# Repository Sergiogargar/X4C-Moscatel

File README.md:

# X4C-Moscatel — Firmware ESP32

Nodo IoT de borde para monitorización de infraestructura ferroviaria.  
Captura la firma vibratoria del tren mediante el IMU ICM-20948, la geolocaliza
con el GPS NEO-6M y publica los datos en tiempo real vía MQTT para alimentar
el dashboard de visualización.

---

## Puesta en marcha

### Requisitos previos

- [ESP-IDF](https://docs.espressif.com/projects/esp-idf/en/latest/esp32s3/get-started/) v5.x instalado y configurado
- Docker + Docker Compose (para el backend)
- El ESP32-S3 conectado por USB

---

### Paso 1 — Obtener la IP del host

El ESP32 publica los datos MQTT al host donde corre Docker.
Antes de compilar, averigua su IP (deben estar en la misma red WiFi):

```bash
# Windows
ipconfig

# Mac / Linux
ifconfig   # o: ip route get 1 | awk '{print $7}'
```

---

### Paso 2 — Configurar el firmware

Abre **`codeina/train_digital_twin/main/network_task.cpp`** y rellena las
macros al inicio del archivo:

```c
// ─── CONFIGURAR ANTES DE FLASHEAR ────────────────────────────────
#define WIFI_SSID       "NOMBRE_DE_TU_RED"        // ← SSID de tu red WiFi
#define WIFI_PASS       "CONTRASEÑA_DE_TU_RED"    // ← Contraseña WiFi
#define MQTT_BROKER_URI "mqtt://192.168.X.X:1883" // ← IP del host del paso 1
#define TRAIN_ID        "T-101"  // ← ID único por unidad (T-101, T-102, ...)
```

> Si tienes varios ESP32, cada uno debe tener un `TRAIN_ID` distinto.

---

### Paso 3 — Arrancar el backend Docker

```bash
cd codeina/train_digital_twin/backend
docker-compose up -d
```

Comprueba que los cuatro contenedores están corriendo:

```bash
docker-compose ps
```

| Servicio | Puerto | Descripción |
|---|---|---|
| Mosquitto | `1883` | Broker MQTT. Recibe los mensajes del ESP32 |
| InfluxDB 2.7 | `8086` | Base de datos. Panel en http://localhost:8086 (`admin` / `adminpassword`) |
| Telegraf | — | Lee el topic MQTT y escribe en InfluxDB |
| Grafana | `3000` | Visualización alternativa en http://localhost:3000 (`admin` / `admin`) |

---

### Paso 4 — Compilar y flashear

```bash
cd codeina/train_digital_twin
idf.py build
idf.py flash
idf.py monitor    # muestra logs serie para verificar conexión WiFi y MQTT
```

O en un solo comando:

```bash
idf.py build flash monitor
```

---

### Paso 5 — Verificar que los datos llegan

Con `idf.py monitor` activo, deberías ver en los logs:

```
I (xxxx) NETWORK_TASK: MQTT Conectado
I (xxxx) NETWORK_TASK: Inicializando Network Task en Core 0
```

Para confirmar que los datos llegan a InfluxDB, abre http://localhost:8086,
entra con `admin` / `adminpassword`, ve a **Data Explorer** y consulta el
bucket `vibrations`. Si hay filas, el pipeline completo funciona.

---

### Referencia rápida de configuración

| Qué cambiar | Archivo | Dónde |
|---|---|---|
| Red WiFi y contraseña | `main/network_task.cpp` | Macros `WIFI_SSID` / `WIFI_PASS` |
| IP del broker MQTT | `main/network_task.cpp` | Macro `MQTT_BROKER_URI` |
| ID del tren | `main/network_task.cpp` | Macro `TRAIN_ID` |
| Umbral de impacto crítico | `main/sensor_task.cpp` | Frecuencia de muestreo y ventana FFT |
| Coordenadas de simulación GPS | `main/telemetry_task.cpp` | Función `parse_nmea()` |

---

## Estructura del firmware

```
codeina/train_digital_twin/
├── main/
│   ├── main.cpp            # Punto de entrada: crea las 4 tareas FreeRTOS
│   ├── data_types.h        # Estructuras de datos compartidas entre tareas
│   ├── telemetry_task.cpp  # Core 0: lee GPS (UART) e IMU (I2C) a 100 Hz
│   ├── sensor_task.cpp     # Core 1: muestreo ADC 10 kHz + FFT 1024 muestras
│   ├── network_task.cpp    # Core 0: WiFi + MQTT → publica JSON al broker
│   └── sd_task.cpp         # Core 0: escribe registros binarios en MicroSD
└── backend/
    ├── docker-compose.yml  # Mosquitto + InfluxDB + Telegraf + Grafana
    ├── mosquitto/config/   # Config del broker MQTT (allow_anonymous)
    └── telegraf/           # telegraf.conf: suscribe MQTT → escribe InfluxDB
```

---

## Flujo de datos

```
ICM-20948 (IMU)  ──┐
                   ├──▶  sensor_task  ──▶  FFT (1024 muestras, 10 kHz)
NEO-6M (GPS)  ─────┘         │                       │
                              │                       ▼
                        telemetry_task         dominant_freq_hz
                              │                       │
                              └───────────────────────┘
                                          │
                                    ProcessedVibrationData_t
                                    (pool de memoria, zero-copy)
                                       ┌──┴──┐
                                       ▼     ▼
                                   SD Task  Network Task
                                   (.bin)       │
                                             MQTT JSON
                                                │
                                          Mosquitto :1883
                                                │
                                           Telegraf
                                                │
                                         InfluxDB :8086
                                                │
                                         Dashboard React
```

### Payload JSON publicado

Cada mensaje MQTT al topic `train/telemetry/vibrations` tiene esta forma:

```json
{
  "timestamp":        1746700000000,
  "lat":              36.6850,
  "lon":              -6.1261,
  "alt":              55.0,
  "accel_z":          10.15,
  "dominant_freq_hz": 42.5,
  "trainId":          "T-101"
}
```

El dashboard convierte `accel_z` (m/s²) a g con `|accel_z − 9.81| / 9.81`
y clasifica el punto como ok / warning / critical según los umbrales definidos en la UI.

---

## Descripción del proyecto

Este es un GEM de Gemini con información completa del proyecto:
https://gemini.google.com/gem/1v8jnuFOj4cJeROFavsBkOiZ2vt1CeKzN?usp=sharing

El proyecto consiste en un nodo **IoT de borde (Edge Computing)** diseñado para
la monitorización de la infraestructura ferroviaria. Su función es capturar la
"firma vibratoria" y la posición geográfica del tren en tiempo real para crear
un modelo digital (Gemelo Digital) que permita predecir fallos en la vía o en
el material rodante.

**Los 3 pilares del Gemelo Digital:**

- **El Objeto Físico:** El tren y la infraestructura (vías, catenarias).
- **El Modelo Virtual:** Representación matemática — modelos de fatiga de materiales, algoritmos de predicción.
- **La Conexión de Datos (aquí entramos nosotros):** El flujo constante de información desde los sensores (ESP32-S3) hacia el modelo virtual.

**Algoritmo en el ESP32-S3:**

1. **Adquisición** — Core 1 muestrea la IMU a 10 kHz. Core 0 lee GPS a 1 Hz y gestiona escritura en SD.
2. **Fusión de datos** — Cada trama FFT se vincula al último GPS conocido mediante mutex FreeRTOS.
3. **FFT** — Ventana Hann de 1024 muestras → 512 bins de frecuencia (resolución ~9.8 Hz/bin, rango 0–5 kHz).
4. **Frecuencia dominante** — Se extrae el bin de mayor energía (ignorando DC) y se envía como `dominant_freq_hz`.
5. **Escritura segura** — SD escribe en bloques cada 100 registros para evitar corrupción ante cortes de energía.

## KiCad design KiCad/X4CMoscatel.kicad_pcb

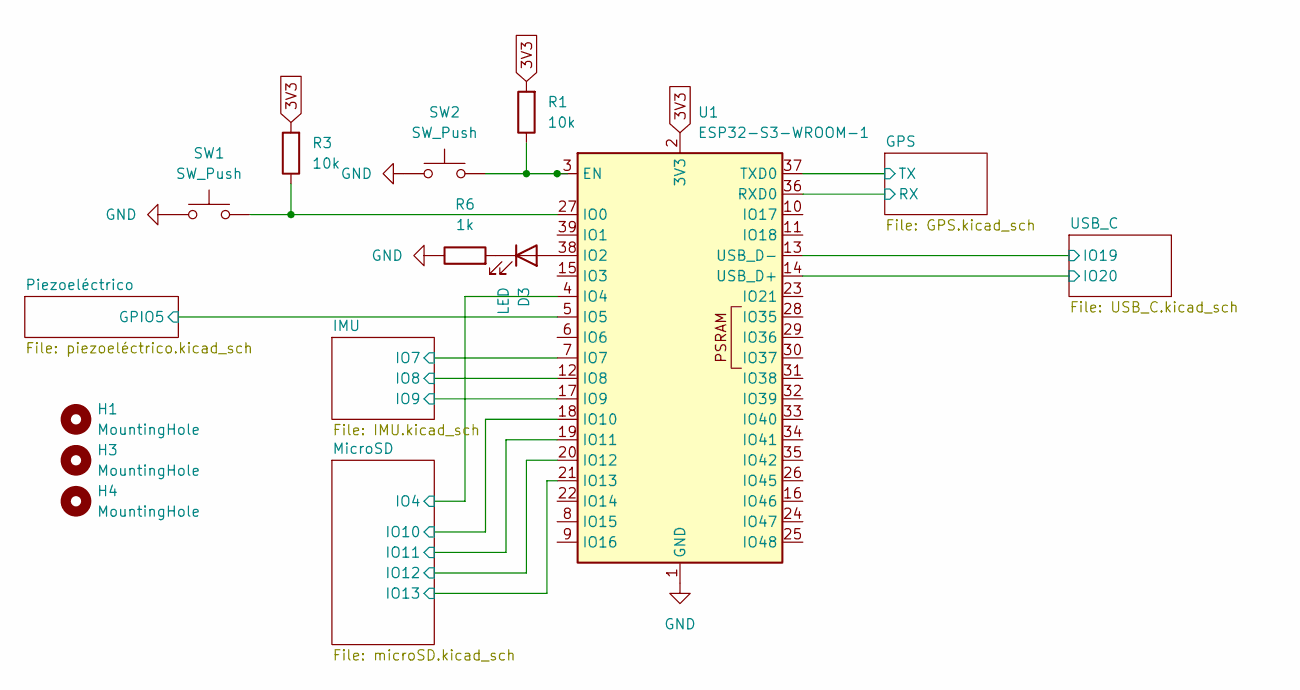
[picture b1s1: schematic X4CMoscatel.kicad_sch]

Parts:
D3: LED; LED_0805_2012Metric
H1, H3, H4: MountingHole; MountingHole_3.2mm_M3
R1, R3: 10k; R_0805_2012Metric
R6: 1k; R_0805_2012Metric
SW1, SW2: SW_Push; SW_Push_SPST_NO_Alps_SKRK
U1: ESP32-S3-WROOM-1

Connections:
3V3: R1.2, R3.2, U1.2 (3V3); also elsewhere on the board
/GPS/RX: U1.36 (RXD0); also elsewhere on the board
/GPS/TX: U1.37 (TXD0); also elsewhere on the board
/IMU/IO7: U1.7 (IO7); also elsewhere on the board
/IMU/IO8: U1.12 (IO8); also elsewhere on the board
/IMU/IO9: U1.17 (IO9); also elsewhere on the board
/MicroSD/IO4: U1.4 (IO4); also elsewhere on the board
/MicroSD/IO10: U1.18 (IO10); also elsewhere on the board
/MicroSD/IO11: U1.19 (IO11); also elsewhere on the board
/MicroSD/IO12: U1.20 (IO12); also elsewhere on the board
/MicroSD/IO13: U1.21 (IO13); also elsewhere on the board
/Piezoeléctrico/GPIO5: U1.5 (IO5); also elsewhere on the board
/USB_C/IO19: U1.13 (USB_D-); also elsewhere on the board
/USB_C/IO20: U1.14 (USB_D+); also elsewhere on the board
GND: R6.1, SW1.1, SW2.1, U1.1 (GND), U1.40 (GND), U1.41 (GND); also elsewhere on the board
unnamed: D3.2 (A), U1.38 (IO2)
unnamed: D3.1 (K), R6.2
unnamed: R1.1, SW2.2, U1.3 (EN)
unnamed: R3.1, SW1.2, U1.27 (IO0)

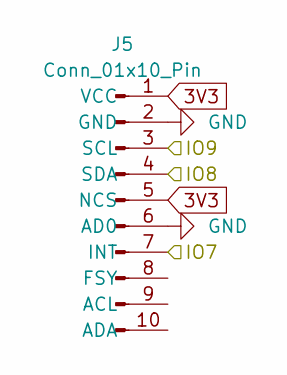
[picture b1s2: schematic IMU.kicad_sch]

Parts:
J5: Conn_01x10_Pin; PinHeader_1x10_P2.54mm_Vertical

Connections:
3V3: J5.1 (VCC), J5.5 (NCS); also elsewhere on the board
/IMU/IO7: J5.7 (INT); also elsewhere on the board
/IMU/IO8: J5.4 (SDA); also elsewhere on the board
/IMU/IO9: J5.3 (SCL); also elsewhere on the board
GND: J5.2 (GND), J5.6 (AD0); also elsewhere on the board

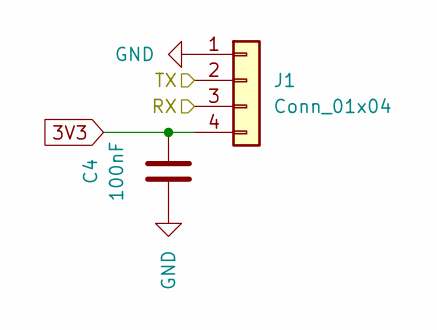
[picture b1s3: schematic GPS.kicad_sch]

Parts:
C4: 100nF; C_0805_2012Metric
J1: Conn_01x04; PinHeader_1x04_P2.54mm_Vertical

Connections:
3V3: C4.2, J1.4; also elsewhere on the board
/GPS/RX: J1.3; also elsewhere on the board
/GPS/TX: J1.2; also elsewhere on the board
GND: C4.1, J1.1; also elsewhere on the board

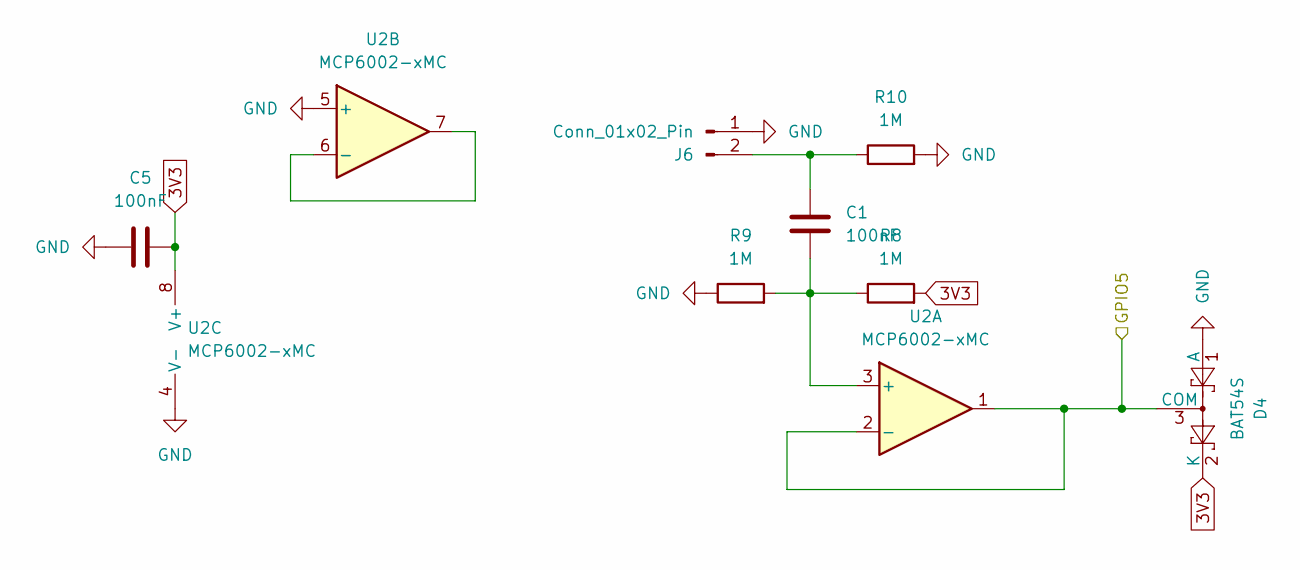
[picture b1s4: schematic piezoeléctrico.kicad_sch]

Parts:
C1, C5: 100nF; C_0805_2012Metric
D4: BAT54S; SOT-23
J6: Conn_01x02_Pin; PinSocket_1x02_P2.54mm_Vertical
R8, R9, R10: 1M; R_0805_2012Metric
U2: MCP6002-xMC; DFN-8-1EP_3x2mm_P0.5mm_EP1.75x1.45mm

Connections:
3V3: C5.1, D4.2 (K), R8.2, U2.8 (V+); also elsewhere on the board
/Piezoeléctrico/GPIO5: D4.3 (COM), U2.1, U2.2 (-); also elsewhere on the board
GND: C5.2, D4.1 (A), J6.1, R9.1, R10.2, U2.4 (V-), U2.5 (+), U2.9 (V-); also elsewhere on the board
unnamed: C1.2, J6.2, R10.1
unnamed: C1.1, R8.1, R9.2, U2.3 (+)
unnamed: U2.6 (-), U2.7

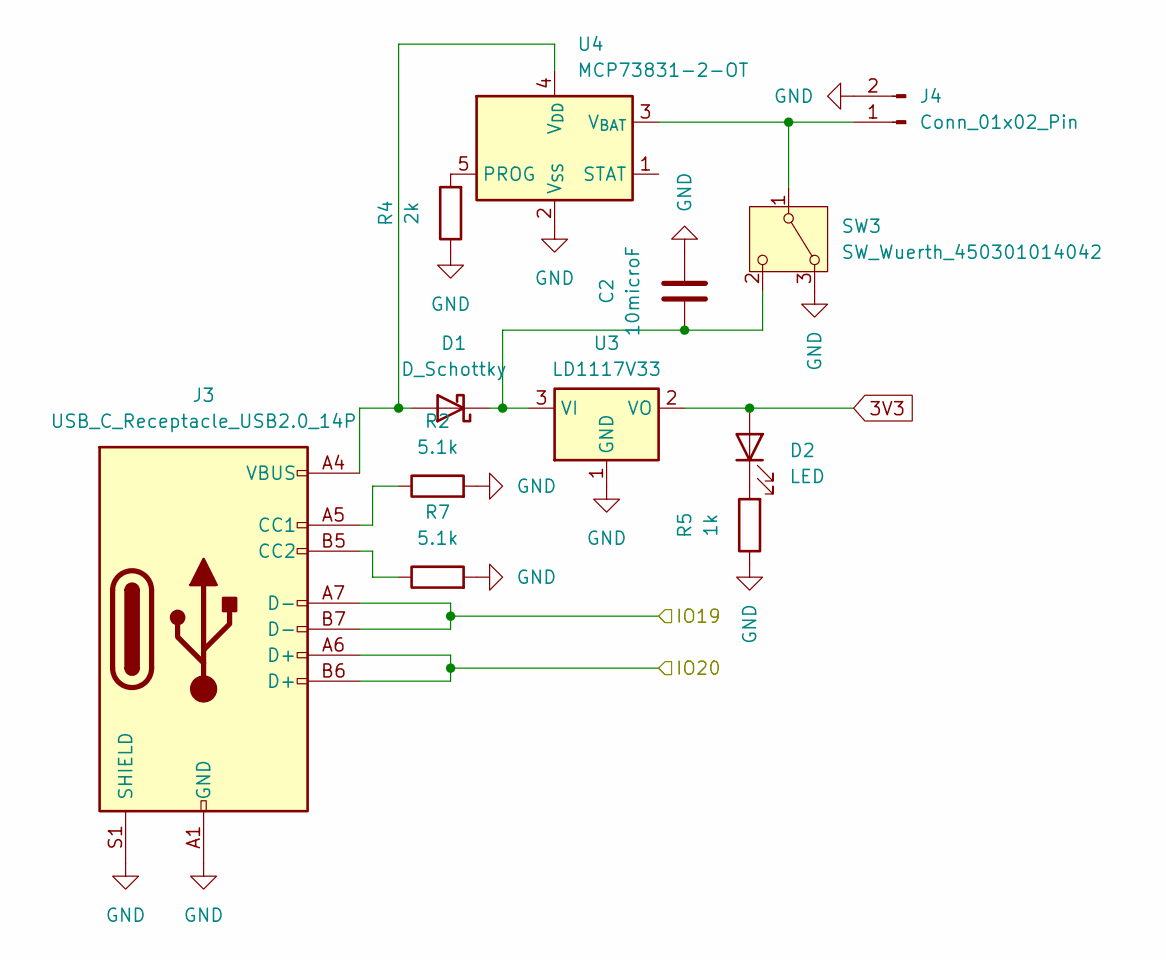
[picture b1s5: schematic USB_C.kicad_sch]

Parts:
C2: 10microF; C_0805_2012Metric
D1: D_Schottky; D_SMA
D2: LED; LED_0805_2012Metric
J3: USB_C_Receptacle_USB2.0_14P; USB_C_Receptacle_HRO_TYPE-C-31-M-12
J4: Conn_01x02_Pin; JST_PH_S2B-PH-K_1x02_P2.00mm_Horizontal
R2, R7: 5.1k; R_0805_2012Metric
R4: 2k; R_0805_2012Metric
R5: 1k; R_0805_2012Metric
SW3: SW_Wuerth_450301014042; SW_Slide-03_Wuerth-WS-SLTV_10x2.5x6.4_P2.54mm
U3: LD1117V33; TO-220-3_Vertical
U4: MCP73831-2-OT; SOT-23-5

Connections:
3V3: D2.2 (A), U3.2 (VO); also elsewhere on the board
/USB_C/IO19: J3.A7 (D-), J3.B7 (D-); also elsewhere on the board
/USB_C/IO20: J3.A6 (D+), J3.B6 (D+); also elsewhere on the board
GND: C2.2, J3.A1 (GND), J3.A12 (GND), J3.B1 (GND), J3.B12 (GND), J3.S1 (SHIELD), J4.2, R2.2, R4.1, R5.1, R7.2, SW3.3 (A), U3.1 (GND), U4.2 (V_{SS}); also elsewhere on the board
unnamed: D1.2 (A), J3.A4 (VBUS), J3.A9 (VBUS), J3.B4 (VBUS), J3.B9 (VBUS), U4.4 (V_{DD})
unnamed: C2.1, D1.1 (K), SW3.2 (C), U3.3 (VI)
unnamed: D2.1 (K), R5.2
unnamed: J3.A5 (CC1), R2.1
unnamed: J3.B5 (CC2), R7.1
unnamed: J4.1, SW3.1 (B), U4.3 (V_{BAT})
unnamed: R4.2, U4.5 (PROG)

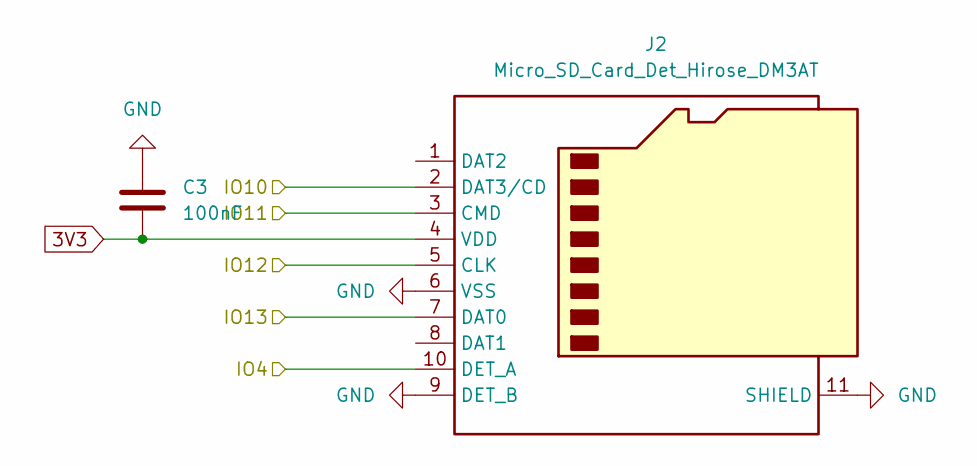
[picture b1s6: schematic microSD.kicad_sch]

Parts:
C3: 100nF; C_0805_2012Metric
J2: Micro_SD_Card_Det_Hirose_DM3AT; microSD_HC_Molex_104031-0811

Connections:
3V3: C3.1, J2.4 (VDD); also elsewhere on the board
/MicroSD/IO4: J2.10 (DET_A); also elsewhere on the board
/MicroSD/IO10: J2.2 (DAT3/CD); also elsewhere on the board
/MicroSD/IO11: J2.3 (CMD); also elsewhere on the board
/MicroSD/IO12: J2.5 (CLK); also elsewhere on the board
/MicroSD/IO13: J2.7 (DAT0); also elsewhere on the board
GND: C3.2, J2.6 (VSS), J2.9 (DET_B), J2.11 (SHIELD); also elsewhere on the board

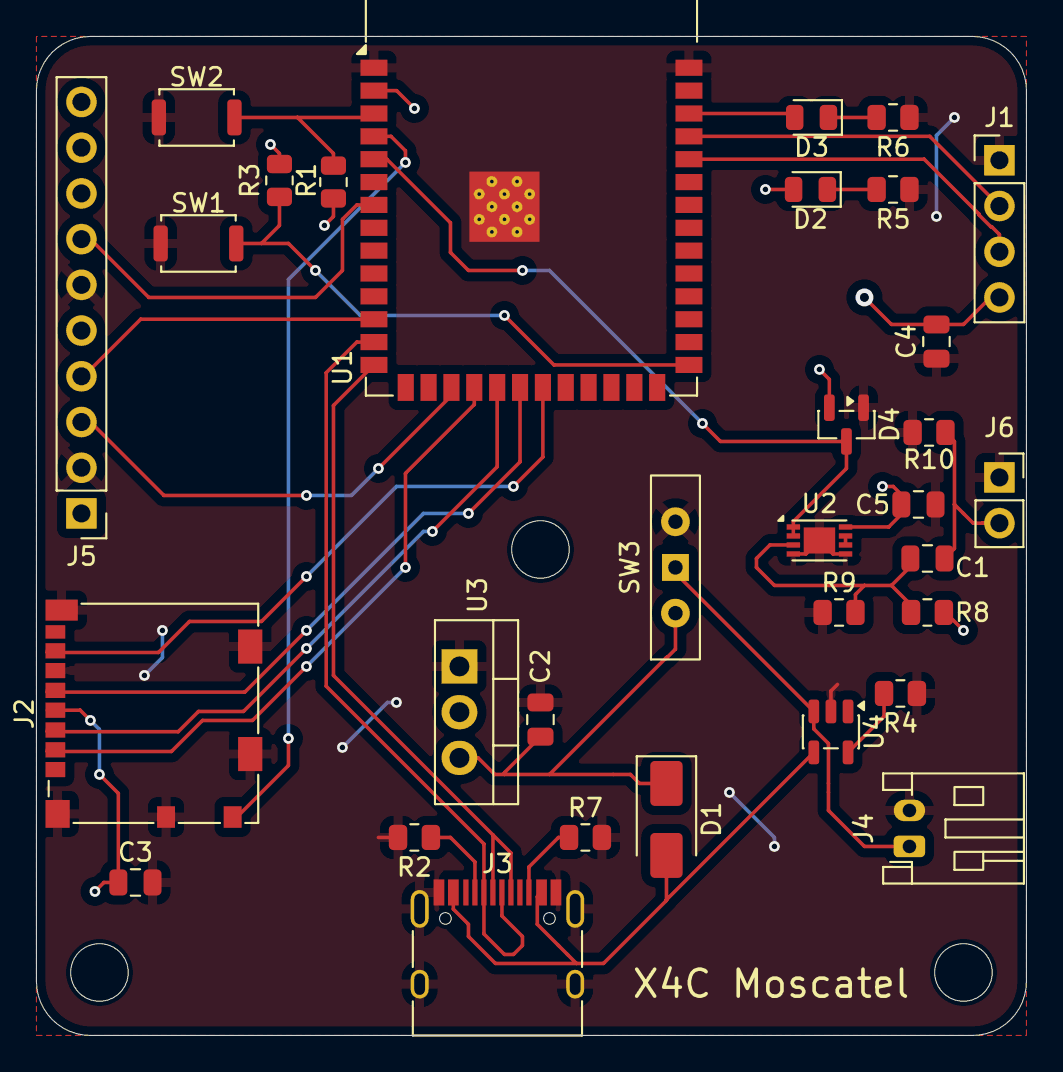
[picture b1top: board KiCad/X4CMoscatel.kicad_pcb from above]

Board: 2 copper layers, 55.0 x 55.5 mm, 35 parts (0 on the bottom side), 29 nets.

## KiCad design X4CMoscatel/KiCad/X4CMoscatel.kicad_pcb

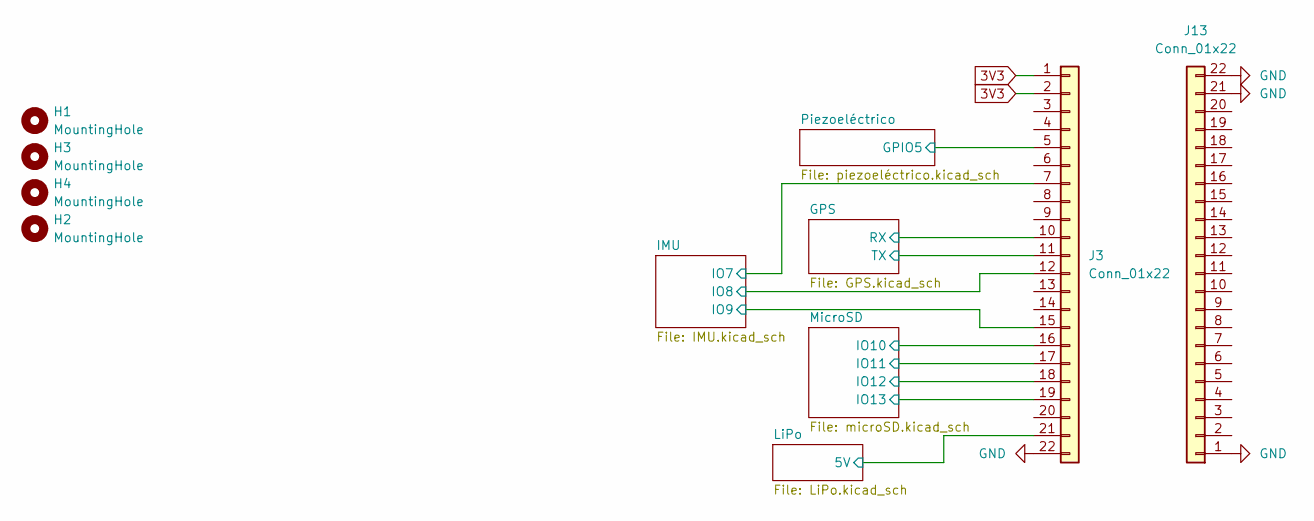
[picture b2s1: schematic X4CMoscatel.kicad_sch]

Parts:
H1, H2, H3, H4: MountingHole; MountingHole_3.2mm_M3
J3, J13: Conn_01x22; PinSocket_1x22_P2.54mm_Vertical

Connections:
3V3: J3.1, J3.2; also elsewhere on the board
/GPS/RX: J3.10; also elsewhere on the board
/GPS/TX: J3.11; also elsewhere on the board
/IMU/IO7: J3.7; also elsewhere on the board
/IMU/IO8: J3.12; also elsewhere on the board
/IMU/IO9: J3.15; also elsewhere on the board
/LiPo/5V: J3.21; also elsewhere on the board
/MicroSD/IO10: J3.16; also elsewhere on the board
/MicroSD/IO11: J3.17; also elsewhere on the board
/MicroSD/IO12: J3.18; also elsewhere on the board
/MicroSD/IO13: J3.19; also elsewhere on the board
/Piezoeléctrico/GPIO5: J3.5; also elsewhere on the board
GND: J3.22, J13.1, J13.21, J13.22; also elsewhere on the board

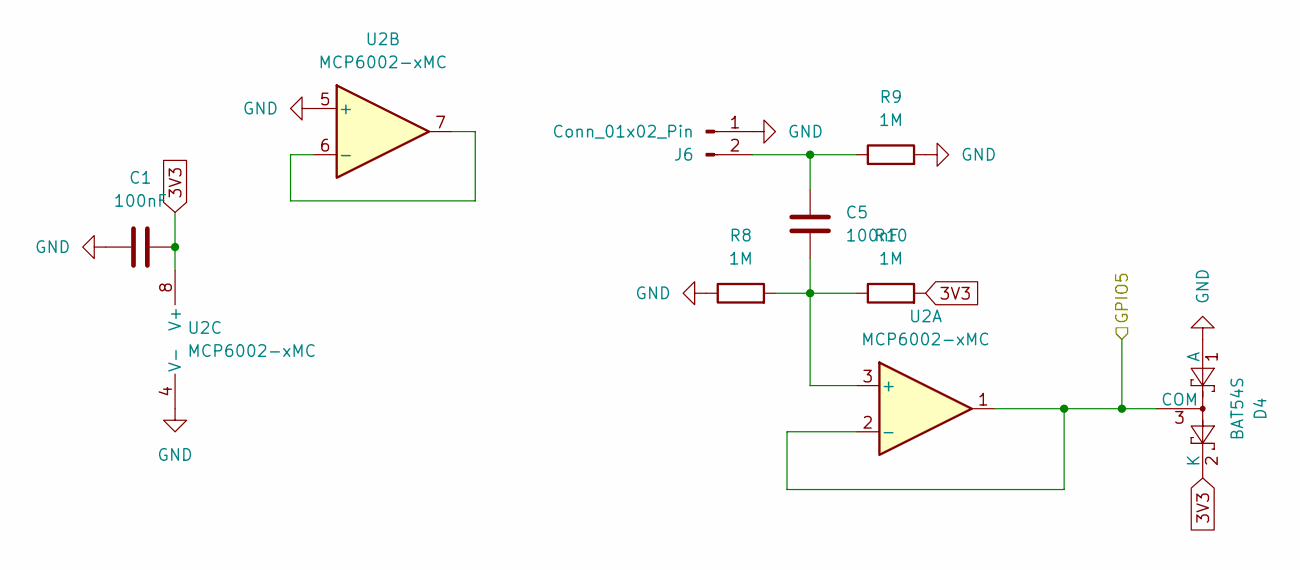
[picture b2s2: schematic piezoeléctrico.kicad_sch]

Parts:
C1, C5: 100nF; C_0805_2012Metric
D4: BAT54S; SOT-23
J6: Conn_01x02_Pin; PinSocket_1x02_P2.54mm_Vertical
R8, R9, R10: 1M; R_0805_2012Metric
U2: MCP6002-xMC; DFN-8-1EP_3x2mm_P0.5mm_EP1.75x1.45mm

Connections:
3V3: C1.1, D4.2 (K), R10.2, U2.8 (V+); also elsewhere on the board
/Piezoeléctrico/GPIO5: D4.3 (COM), U2.1, U2.2 (-); also elsewhere on the board
GND: C1.2, D4.1 (A), J6.1, R8.1, R9.2, U2.4 (V-), U2.5 (+), U2.9 (V-); also elsewhere on the board
unnamed: C5.2, J6.2, R9.1
unnamed: C5.1, R8.2, R10.1, U2.3 (+)
unnamed: U2.6 (-), U2.7

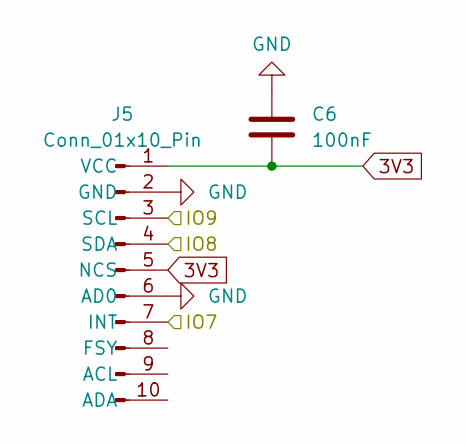
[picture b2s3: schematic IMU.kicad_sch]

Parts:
C6: 100nF; C_0805_2012Metric
J5: Conn_01x10_Pin; PinHeader_1x10_P2.54mm_Vertical

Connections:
3V3: C6.1, J5.1 (VCC), J5.5 (NCS); also elsewhere on the board
/IMU/IO7: J5.7 (INT); also elsewhere on the board
/IMU/IO8: J5.4 (SDA); also elsewhere on the board
/IMU/IO9: J5.3 (SCL); also elsewhere on the board
GND: C6.2, J5.2 (GND), J5.6 (AD0); also elsewhere on the board

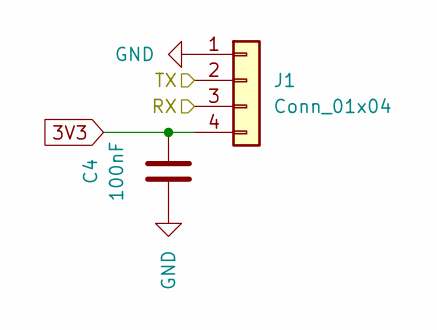
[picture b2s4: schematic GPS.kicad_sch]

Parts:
C4: 100nF; C_0805_2012Metric
J1: Conn_01x04; PinHeader_1x04_P2.54mm_Vertical

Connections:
3V3: C4.2, J1.4; also elsewhere on the board
/GPS/RX: J1.3; also elsewhere on the board
/GPS/TX: J1.2; also elsewhere on the board
GND: C4.1, J1.1; also elsewhere on the board

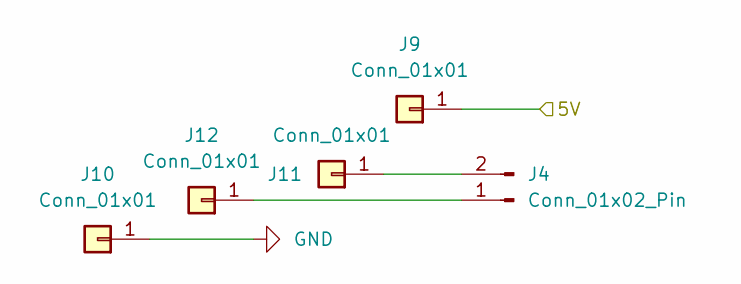
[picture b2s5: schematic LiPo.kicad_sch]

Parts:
J4: Conn_01x02_Pin; JST_PH_S2B-PH-K_1x02_P2.00mm_Horizontal
J9, J10, J11, J12: Conn_01x01; PinHeader_1x01_P2.54mm_Vertical

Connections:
/LiPo/5V: J9.1; also elsewhere on the board
GND: J10.1; also elsewhere on the board
unnamed: J4.2, J11.1
unnamed: J4.1, J12.1

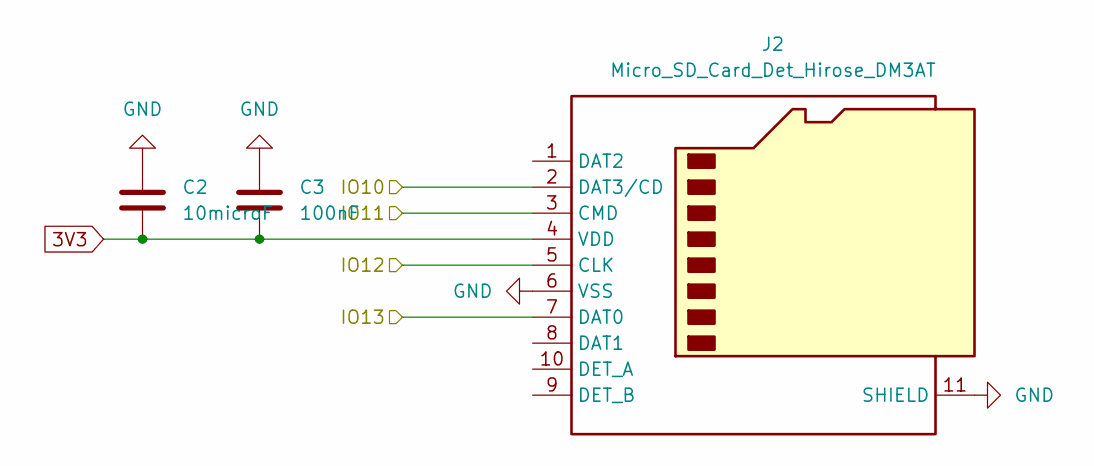
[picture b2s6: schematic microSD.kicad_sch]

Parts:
C2: 10microF; C_0805_2012Metric
C3: 100nF; C_0805_2012Metric
J2: Micro_SD_Card_Det_Hirose_DM3AT; microSD_HC_Molex_104031-0811

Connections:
3V3: C2.1, C3.1, J2.4 (VDD); also elsewhere on the board
/MicroSD/IO10: J2.2 (DAT3/CD); also elsewhere on the board
/MicroSD/IO11: J2.3 (CMD); also elsewhere on the board
/MicroSD/IO12: J2.5 (CLK); also elsewhere on the board
/MicroSD/IO13: J2.7 (DAT0); also elsewhere on the board
GND: C2.2, C3.2, J2.6 (VSS), J2.11 (SHIELD); also elsewhere on the board

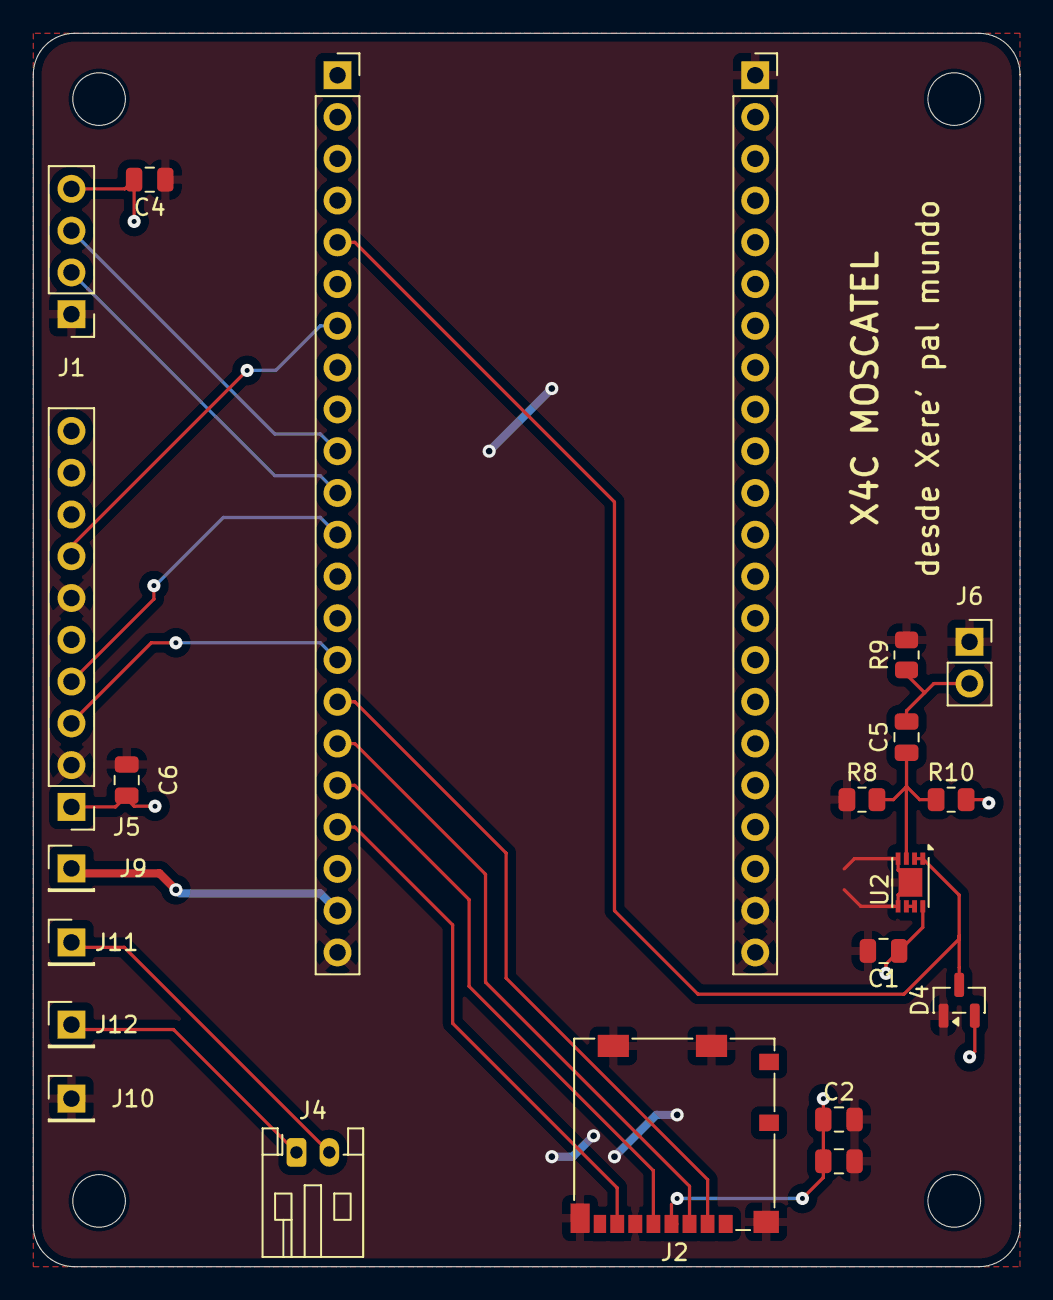
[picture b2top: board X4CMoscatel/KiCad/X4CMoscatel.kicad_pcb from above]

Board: 2 copper layers, 60.0 x 75.0 mm, 26 parts (0 on the bottom side), 18 nets.

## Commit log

2026-02-16 Carpeta KiCad
2026-05-08 Upgrade tocho
2026-05-08 Add dominant_freq to telemetry and backend
    Compute and publish FFT dominant frequency end-to-end: add dominant_freq_hz to TelemetryData_t, compute dominant bin in sensor_task, and include dominant_freq_hz + trainId in MQTT JSON. Network task 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
2026-06-14 cosas sergito
2026-06-15 cambios miguel
2026-06-15 gitignore for build
